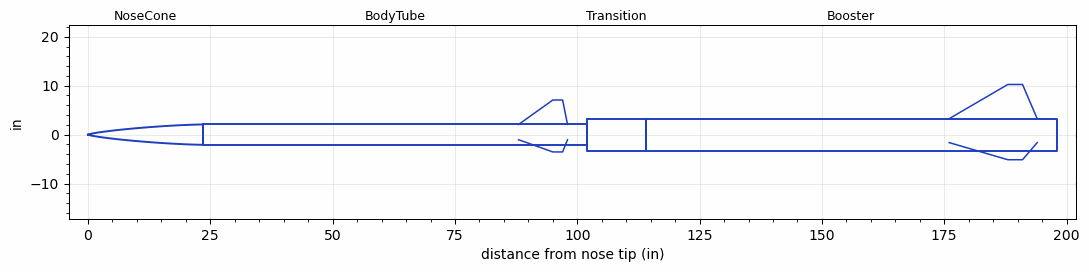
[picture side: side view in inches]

<RASAeroDocument>
 <FileVersion>2</FileVersion>
 <RocketDesign>
  <NoseCone>
   <Length>23.5</Length>
   <Diameter>4.1534</Diameter>
   <Shape>Von Karman Ogive</Shape>
   <Location>0</Location>
  </NoseCone>
  <BodyTube>
   <Length>78.5</Length>
   <Diameter>4.1534</Diameter>
   <Location>23.5</Location>
   <Fin>
    <Count>3</Count>
    <Chord>10</Chord>
    <Span>5</Span>
    <SweepDistance>7</SweepDistance>
    <TipChord>2</TipChord>
    <Thickness>0.125</Thickness>
    <Location>14</Location>
    <AirfoilSection>Square</AirfoilSection>
   </Fin>
  </BodyTube>
  <Transition>
   <Length>12</Length>
   <Diameter>6.51</Diameter>
   <Location>102</Location>
   <RearDiameter>6.51</RearDiameter>
  </Transition>
  <Booster>
   <Length>84</Length>
   <Diameter>6.51</Diameter>
   <InsideDiameter>6.51</InsideDiameter>
   <Location>114</Location>
   <ShoulderLength>0</ShoulderLength>
   <Fin>
    <Count>3</Count>
    <Chord>18</Chord>
    <Span>7</Span>
    <SweepDistance>12</SweepDistance>
    <TipChord>3</TipChord>
    <Thickness>0.125</Thickness>
    <Location>22</Location>
    <AirfoilSection>Square</AirfoilSection>
   </Fin>
  </Booster>
  <Surface>Smooth (Zero Roughness)</Surface>
  <ModifiedBarrowman>False</ModifiedBarrowman>
  <Turbulence>False</Turbulence>
  <UseBooster1>False</UseBooster1>
  <UseBooster2>False</UseBooster2>
 </RocketDesign>
 <LaunchSite>
  <Altitude>0</Altitude>
  <Pressure>0</Pressure>
  <RodAngle>0</RodAngle>
  <RodLength>4</RodLength>
  <Temperature>74</Temperature>
  <WindSpeed>0</WindSpeed>
 </LaunchSite>
 <Recovery>
  <Altitude1>1000</Altitude1>
  <Altitude2>1000</Altitude2>
  <DeviceType1>None</DeviceType1>
  <DeviceType2>None</DeviceType2>
  <Event1>False</Event1>
  <Event2>False</Event2>
  <Size1>1</Size1>
  <Size2>1</Size2>
  <EventType1>None</EventType1>
  <EventType2>None</EventType2>
  <CD1>1.33</CD1>
  <CD2>1.33</CD2>
 </Recovery>
 <SimulationList>
  <Simulation>
   <SustainerEngine>BERMA-25000-02  (Karman_AIAA-capstone)</SustainerEngine>
   <SustainerLaunchWt>52</SustainerLaunchWt>
   <SustainerNozzleDiameter>4</SustainerNozzleDiameter>
   <SustainerCG>70</SustainerCG>
   <SustainerIgnitionDelay>24</SustainerIgnitionDelay>
   <Booster1Engine>O8000  (CTI)</Booster1Engine>
   <Booster1LaunchWt>146</Booster1LaunchWt>
   <Booster1SeparationDelay>0</Booster1SeparationDelay>
   <Booster1IgnitionDelay>0</Booster1IgnitionDelay>
   <Booster1CG>130</Booster1CG>
   <Booster1NozzleDiameter>6</Booster1NozzleDiameter>
   <IncludeBooster1>True</IncludeBooster1>
   <Booster2Delay>0</Booster2Delay>
   <IncludeBooster2>False</IncludeBooster2>
   <TimetoApogee>149.7898</TimetoApogee>
   <MaxAltitude>257381.4</MaxAltitude>
   <MaxVelocity>4828.892</MaxVelocity>
   <OptimumWt>32.94688</OptimumWt>
   <OptimumMaxAlt>32.94688</OptimumMaxAlt>
  </Simulation>
  <Simulation>
   <SustainerEngine>BERMA-25000-02  (Karman_AIAA-capstone)</SustainerEngine>
   <SustainerLaunchWt>45</SustainerLaunchWt>
   <SustainerNozzleDiameter>4</SustainerNozzleDiameter>
   <SustainerCG>70</SustainerCG>
   <SustainerIgnitionDelay>24</SustainerIgnitionDelay>
   <Booster1Engine>O8000  (CTI)</Booster1Engine>
   <Booster1LaunchWt>130</Booster1LaunchWt>
   <Booster1SeparationDelay>0</Booster1SeparationDelay>
   <Booster1IgnitionDelay>0</Booster1IgnitionDelay>
   <Booster1CG>130</Booster1CG>
   <Booster1NozzleDiameter>6</Booster1NozzleDiameter>
   <IncludeBooster1>True</IncludeBooster1>
   <Booster2Delay>0</Booster2Delay>
   <IncludeBooster2>False</IncludeBooster2>
   <TimetoApogee>182.3619</TimetoApogee>
   <MaxAltitude>393166.6</MaxAltitude>
   <MaxVelocity>5967.052</MaxVelocity>
   <OptimumWt>31.35938</OptimumWt>
   <OptimumMaxAlt>31.35938</OptimumMaxAlt>
  </Simulation>
 </SimulationList>
</RASAeroDocument>
